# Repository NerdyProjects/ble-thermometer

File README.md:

# Bluetooth Low Energy Thermometer

This project describes a bluetooth low energy thermometer.

All code licenced as GPLv3, all documentation and PCB as CC0.

## Purpose
### Conceptual idea: fertility awareness method thermometer

The fertility awareness method, especially the symptothermal method, is a method to classify a woman's fertility by carefully monitoring symptoms of the body to be able to know in which state of the menstrual cycle she is.
One of the monitored symptoms is the body temperature:
The fundamental body temperature is normally taken early in the morning, directly after waking up after a restful sleep.
Women using this method, mostly use a clinical thermometer that has two digits, so a resolution of 0.01 °C.
To get an accurate measurement, measuring inside the vagina or the anus for at least 2 minutes is strongly recommended.
Because of practical reason, most chose to measure inside the vagina.

As a fan of natural birth control, I wanted to support woman by providing a device that relieves them of some stress of the temperature measurement as well as provides additional, maybe interesting data:
  * Not having to think about measuring the temperature in the morning
  * Not having to set an alarm for the same time (for some people the measurement time has a strong influence on the temperature, so you should always measure at a similar time)
  * Being able to detect factors that change your temperature more easily
  * Maybe even providing a better safety of the method by providing more data
  * Not having to immediately write down the measurement result

So the idea was born:
A thermometer, 
  * that can be inserted into the vagina
    * over night
    * the whole day
    * maybe even just in the early morning for some minutes
  * that records and stores the temperature
  * that can be read out using a smartphone or a computer
  * where there is high value on the ease of use as well as user privacy (no cloud service)
  * that does not hide the complexity of the symptothermal method (e.g. ONLY a thermometer, not a full birth control solution)

Initially, I wrote down more thoughts in a [design.md](design document) which is very far from how reality evolved.

I decided to go for the following system design:
  * Battery powered device powered by the ST SPBTLE-1S Bluetooth low Energy System-on-Chip application processor
  * Bosch BMP280 temperature/pressure sensor (because its high accuracy, low power usage, ease of use and my experience with it)
  * BR1632 lithium coin cell (because of availability as high temperature device)
  * altogether put on a small pcb surrounded by silicone to be completely safe to be used in contact with skin or mucous membrane

This design has a few limitations that are clear even before the first prototype has been built:
  * Limited battery lifetime: Device becomes unusable after ~1-3 years
    * Battery can be exchanged by replacing the silicone
  * High price: Pure materials cost ~15 € per piece
  * Silicone mould might need fiddling a bit

## Prototype

## System architecture
The SPBTLE-1S is a System-on-Chip including a Cortex M0 processor, some flash and Ram, typical microcontroller peripherals and a bluetooth low energy radio.
The bluetooth low energy radio comes with a proprietary, binary-only library, that is linked to the custom user program and provides high level methods to configure the bluetooth part of the device as well as transfer data.

Different libraries are provided by ST that allow creating a running application easily.

The device contains two softwares:
  * The OTA Service Manager, which openly listens for bluetooth connections to reprogram the firmware. It is started after powerup and automatically boots the application software after some seconds.
  * The actual application software. It implements a "safety feature" Long pressing the button (for > 25 seconds) resets the chip, starting in the OTA Service Manager.

## Theory of operation
The thermometer device has different operating modes, whereby it should be kept in mind that the device itself can never be completely powered off.

  * Standby: Time-tracking mode, just counts how long in the past the last measurement has been taken. Can be woken up by button press.
  * Recording: The device takes a measurement point in a fixed (but configurable) interval. Up to 4096 points can be stored before the oldest one gets overwritten.
  * Connectable: The device advertises its Bluetooth low Energy services and is connectable by a paired device. As this mode takes quite some power, it should only be active for a short time.
  * Connected: The device is connected to another device. Data can be read out, configuration can be changed. This mode also takes a bit more power and should only be active for a short time.
  * Pairable: The device advertises its services and is connectable and pairable by other devices.

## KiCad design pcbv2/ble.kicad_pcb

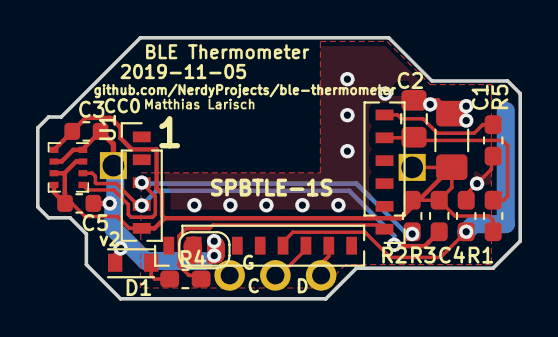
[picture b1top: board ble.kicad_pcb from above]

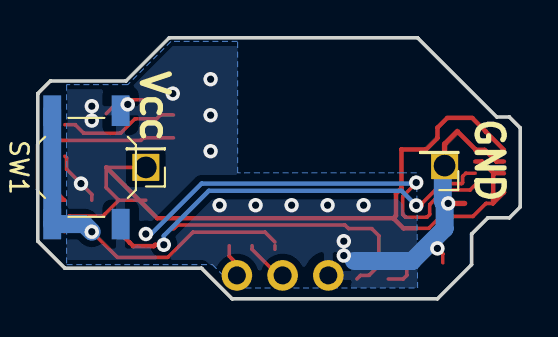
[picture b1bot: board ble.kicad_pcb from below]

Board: 2 copper layers, 26.8 x 14.5 mm, 20 parts (3 on the bottom side), 12 nets.

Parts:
C1: 100µ/6,3V; C_1206_3216Metric_Pad1.42x1.75mm_HandSolder
C2: 10µ; C_0805_2012Metric_Pad1.15x1.40mm_HandSolder
C3, C5: 100n; C_0603_1608Metric
C4: 100n; C_0603_1608Metric_Pad1.05x0.95mm_HandSolder
D1: VLMO20J2M1-GS08; LED_miniPLCC_2315
J1: Conn_01x05; PinHeader_1x05_P1.27mm_Vertical
J2: Conn_01x09; PinHeader_1x09_P1.27mm_Vertical
J3: Conn_01x06; PinHeader_1x06_P1.27mm_Vertical
J4: Conn_01x03; PinHeader_1x03_P2.54mm_Vertical
J5, J6: Conn_01x01; PinHeader_1x01_P2.00mm_Vertical
JP1: BOOT; SolderJumper-2_P1.3mm_Open_RoundedPad1.0x1.5mm
R1: 47k; R_0603_1608Metric_Pad1.05x0.95mm_HandSolder
R2, R3: 4k7; R_0603_1608Metric_Pad1.05x0.95mm_HandSolder
R4: 470; R_0603_1608Metric_Pad1.05x0.95mm_HandSolder
R5: 10k; R_0603_1608Metric_Pad1.05x0.95mm_HandSolder
SW1: SW_Push; SW_SPST_TL3342
U1: BMP280; Bosch_LGA-8_2x2.5mm_P0.65mm_ClockwisePinNumbering

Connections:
GND: C1.2, C2.2, C3.2, C4.2, C5.2, D1.1, J2.3, J4.3, J6.1, JP1.1, R5.1, SW1.2, U1.1, U1.7
unnamed: C4.1, J2.6, SW1.1
unnamed: D1.2, R4.1
unnamed: J2.2, JP1.2
unnamed: J3.1, R4.2
unnamed: J3.6, R5.2
RESET_N: C2.1, J3.5, R1.2
SCL: J1.3, R2.2, U1.4
SDA: J1.4, R3.2, U1.3
SWCLK: J2.7, J4.2
SWDIO: J2.8, J4.1
VCC: C1.1, C3.1, C5.1, J1.5, J5.1, R1.1, R2.1, R3.1, U1.2, U1.5, U1.6, U1.8

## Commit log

2018-03-11 Design document and pcb v0.1
2018-03-11 Draft readme
2018-03-12 Add github note
2018-04-01 Add pcb image
2019-01-28 First compilable scafolding with Makefile
    This copied some code from BLE_SensorDemo, stripped every function and
    use parameters and files gathered through a TrueStudio compilation.
    Makefile supported by cm-makefile, which can be used unmodified.
    The generated binary is not yet tested and will not do anything useful.
2019-01-28 Add original service manager
2019-01-28 Relax warning on compilation
2019-01-28 Add default reset manager
2019-02-03 Runnable OTA application
2019-02-03 Working reset manager
2019-02-03 Initial Bosch bmp280 lib
2019-02-03 Working proof of concept thermometer node
2019-02-03 Working ServiceManager
2019-02-03 ServiceManager supports bootloader timeout
    ServiceManager adapted so bootloader stays active before application
    load. Also, flash erase happens on write_image characteristic, so before
    a flash write.
    This should be tested, but theoretically recover from broken firmware
    images.
    Watchdog is activated before control is passed to firmware.
2019-02-03 Refactor application
2019-02-06 3d model of second prototype
2019-02-08 Add drill holes
2019-02-10 Add screw holes to Cad model
2019-03-05 Fix ServiceManager boot logic and WDG timeout
2019-03-05 Exclude build folder from git
2019-03-05 Fix Watchdog reset in application
2019-03-07 increase form size quite a bit
2019-03-09 Faster application load time, longer adv. int.
2019-03-09 Add debug uart
2019-03-09 longer adv. interval
2019-03-12 draft of pc tool
2019-03-12 optimized mill form
2019-03-12 serial debug, temperature history, button, battery
2019-03-12 prototype characteristics/errata
2019-03-12 missing source files
2019-03-12 detect end of data
2019-03-15 decrease size, button marker, more stability
2019-03-18 Change settings from PC application
2019-03-18 Update pcb errata
2019-03-18 Implement temperature recording
2019-03-21 Code style
2019-03-21 Track time interval between stop/start measurement
2019-03-22 Fix sensor timer stopped on measurement stopped
2019-03-22 Allow configuring connection timeouts/options
2019-03-22 more power efficient LED patterns
2019-03-22 properly sleep while button is pressed
2019-03-22 reveal more internal state on BLE interface
2019-03-22 Add some forgotten files...
2019-03-22 fix time tracking calculation
2019-03-22 update python app protocol
2019-03-22 Add more status output
2019-03-22 reverse recorder readout order to simplify time
2019-03-22 Fix mistake
2019-03-24 read all status data
2019-03-24 try lowering vtimer delta times
    I observed problems looking like overflows (time sometimes stepped
    forward in N*5242 second steps which is the maximum allowed delta time
    and ~half the value of the timer.)
2019-03-25 tick BTLE stack directly after wakeup
2019-03-25 Writeup some thoughts about BLE internals
2019-03-25 Add feedback to CAD model
2019-03-27 debug, faster UART, move vtimer access to tick
2019-03-30 fix image link
2019-04-25 Update some documents
2019-04-25 Remove debug flag
2019-04-29 Implement time based recorder readout
2019-04-29 Allow measurement to be enabled without recording
2019-04-29 Fix detection for invalid ring blocks
2019-04-29 Only start/stop measurement if (not) running
2019-11-04 PCB v2
2019-11-05 Add second bme capacitor
